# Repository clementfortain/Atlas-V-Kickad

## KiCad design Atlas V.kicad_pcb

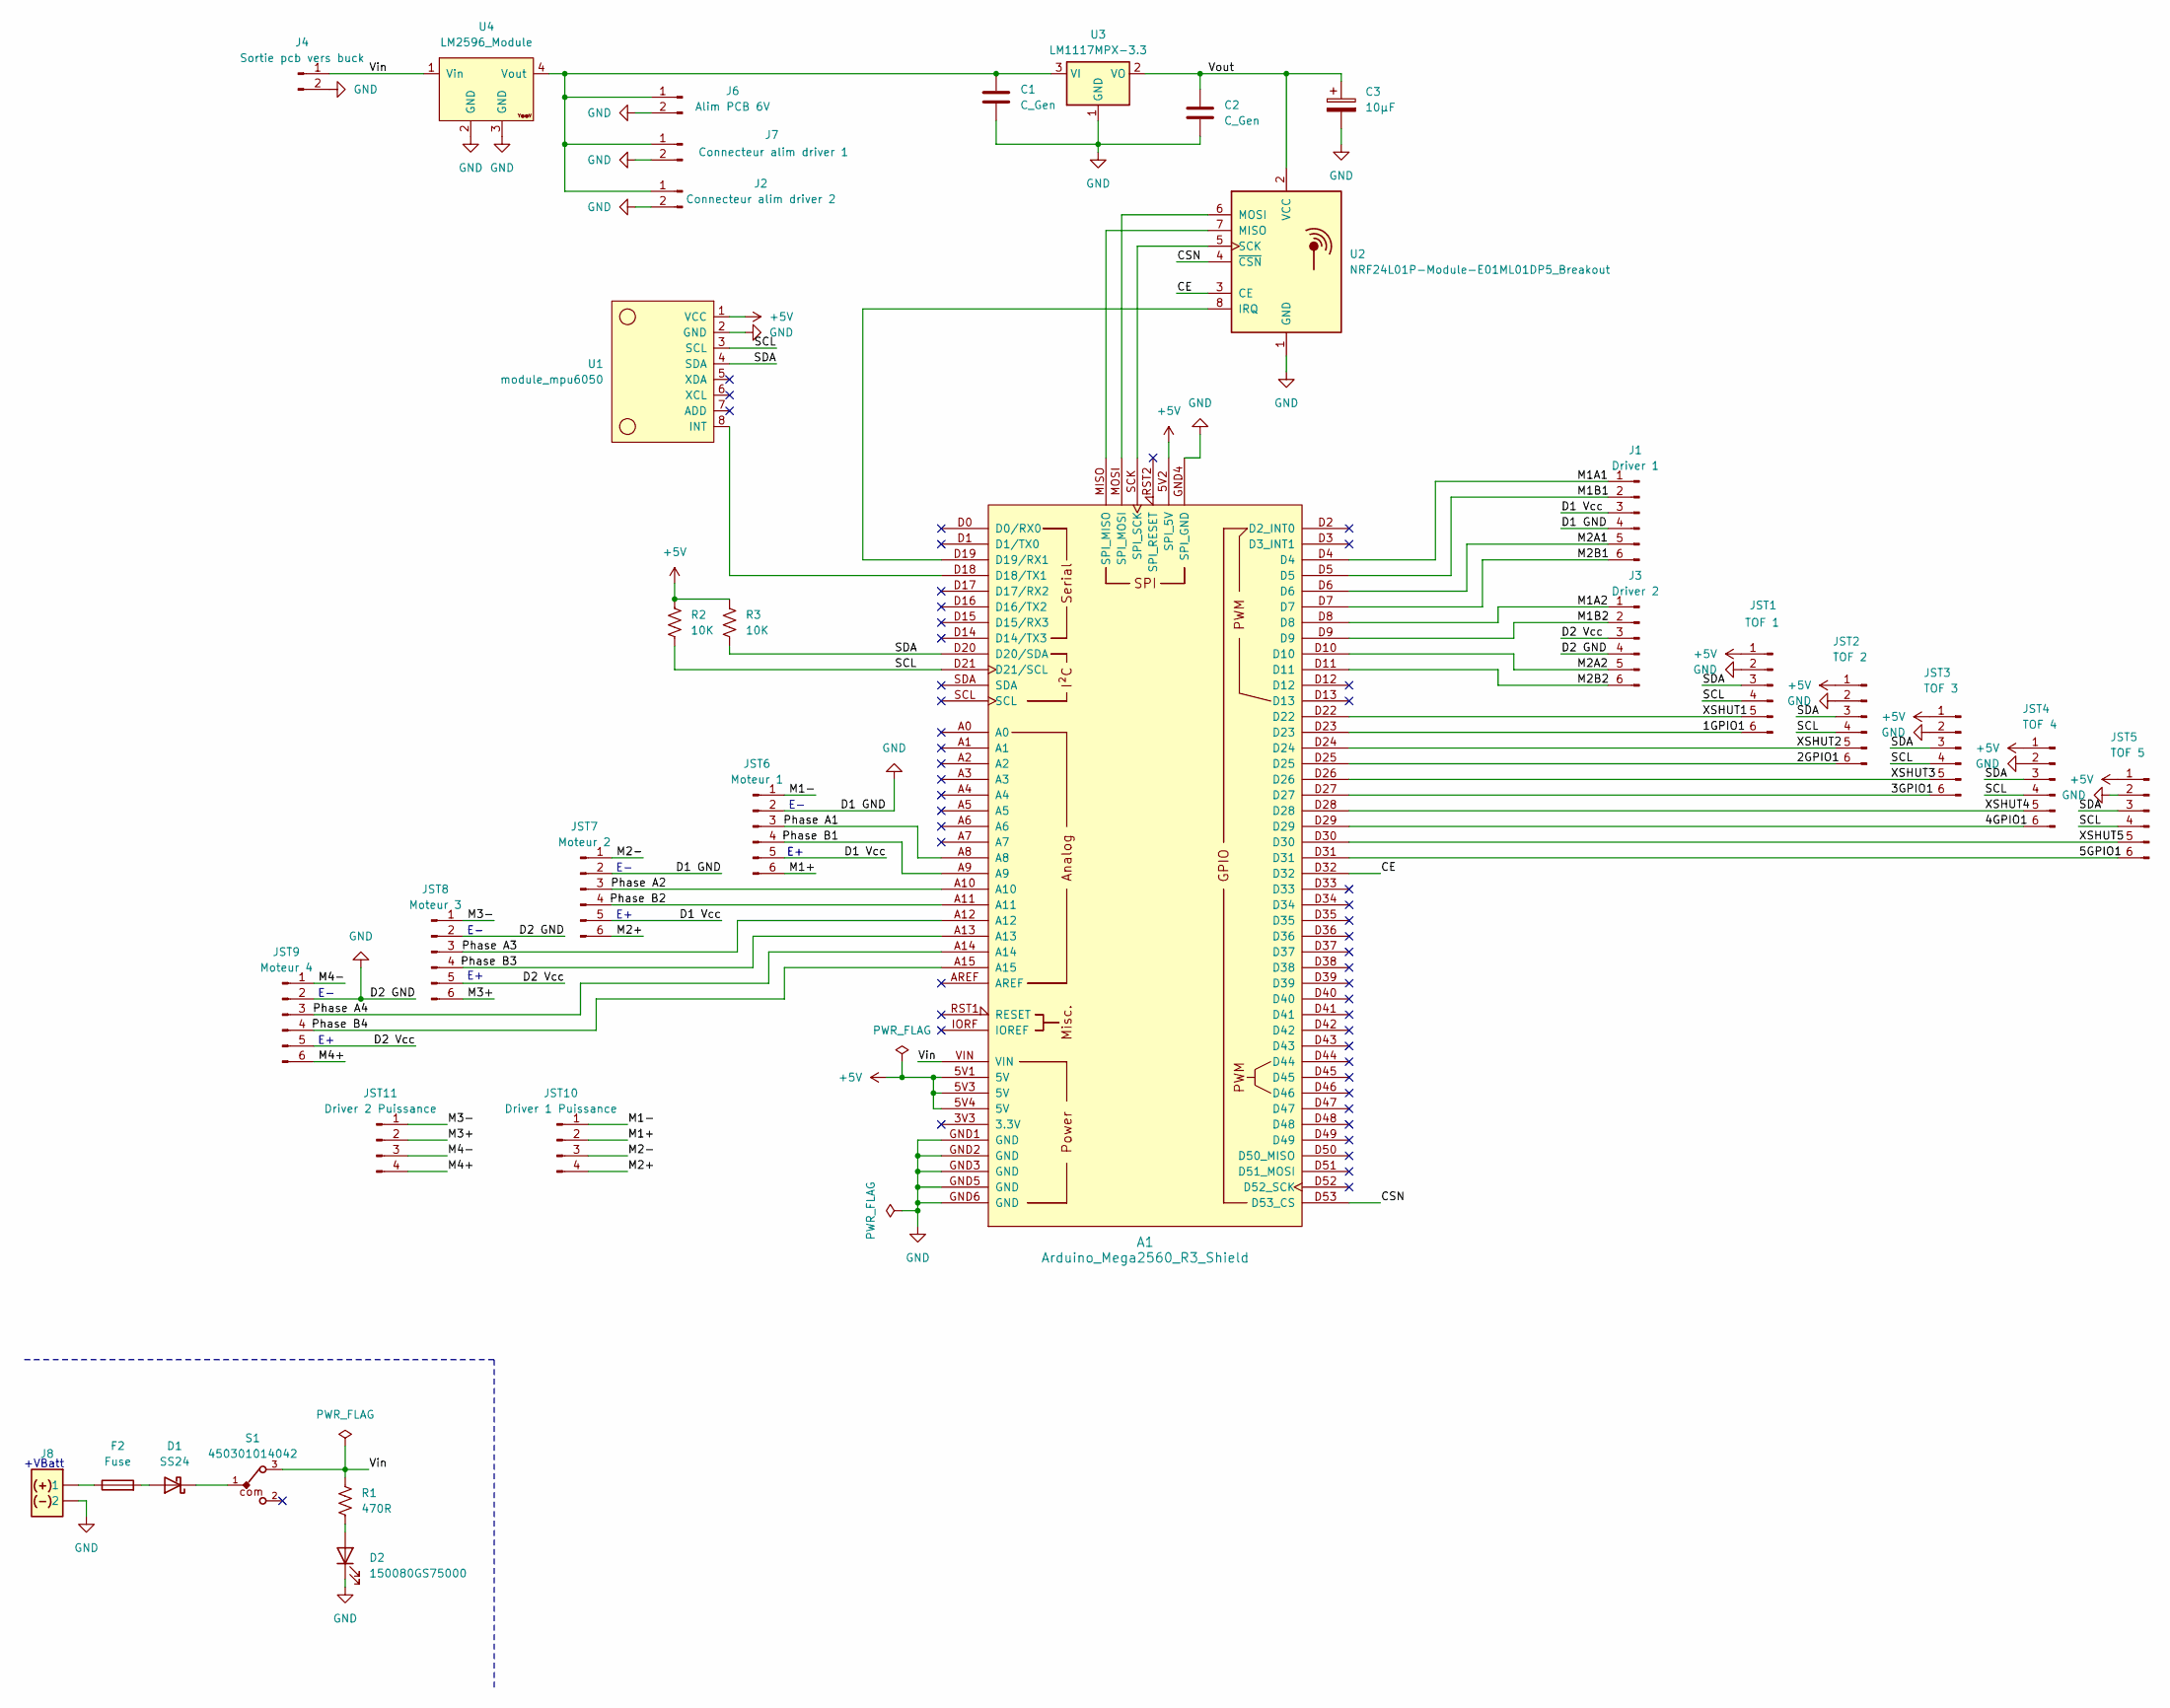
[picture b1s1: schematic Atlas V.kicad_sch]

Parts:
A1: Arduino_Mega2560_R3_Shield; Arduino_Mega2560_R3_Shield_LongPad
C1, C2: C_Gen; C_1206_3216Metric_Pad1.33x1.80mm_HandSolder
C3: 10µF; CP_EIA-6032-28_Kemet-C_Pad2.25x2.35mm_HandSolder
D1: SS24; D_SMB_Handsoldering
D2: 150080GS75000; LED_0805_2012Metric_Pad1.15x1.40mm_HandSolder
F2: Fuse; Fuseholder_TR5_Littelfuse_No560_No460
J1: Driver 1; JST_XH_B6B-XH-AM_1x06_P2.50mm_Long_Vertical
J2: Connecteur alim driver 2; JST_XH_B2B-XH-AM_1x02_P2.50mm_Long_Vertical
J3: Driver 2; JST_XH_B6B-XH-AM_1x06_P2.50mm_Long_Vertical
J4: Sortie pcb vers buck; JST_XH_B2B-XH-AM_1x02_P2.50mm_Long_Vertical
J6: Alim PCB 6V; JST_XH_B2B-XH-AM_1x02_P2.50mm_Long_Vertical
J7: Connecteur alim driver 1; JST_XH_B2B-XH-AM_1x02_P2.50mm_Long_Vertical
J8: CON 1x2 POLARIZED; AMASS_XT60-M_1x02_P7.20mm_Vertical
JST1: TOF 1; JST_XH_B6B-XH-AM_1x06_P2.50mm_Long_Vertical
JST2: TOF 2; JST_XH_B6B-XH-AM_1x06_P2.50mm_Long_Vertical
JST3: TOF 3; JST_XH_B6B-XH-AM_1x06_P2.50mm_Long_Vertical
JST4: TOF 4; JST_XH_B6B-XH-AM_1x06_P2.50mm_Long_Vertical
JST5: TOF 5; JST_XH_B6B-XH-AM_1x06_P2.50mm_Long_Vertical
JST6: Moteur 1; JST_XH_B6B-XH-AM_1x06_P2.50mm_Long_Vertical
JST7: Moteur 2; JST_XH_B6B-XH-AM_1x06_P2.50mm_Long_Vertical
JST8: Moteur 3; JST_XH_B6B-XH-AM_1x06_P2.50mm_Long_Vertical
JST9: Moteur 4; JST_XH_B6B-XH-AM_1x06_P2.50mm_Long_Vertical
JST10: Driver 1 Puissance; JST_XH_B4B-XH-AM_1x04_P2.50mm_Long_Vertical
JST11: Driver 2 Puissance; JST_XH_B4B-XH-AM_1x04_P2.50mm_Long_Vertical
R1: 470R; R_1206_3216Metric_Pad1.30x1.75mm_HandSolder
R2: 10K; R_1206_3216Metric_Pad1.30x1.75mm_HandSolder
R3: 10K; R_1206_3216Metric_Pad1.30x1.75mm_HandSolder; PartNumber Voir farde de resistance
S1: 450301014042
U1: module_mpu6050
U2: NRF24L01P-Module-E01ML01DP5_Breakout; E01-ML01DP5
U3: LM1117MPX-3.3; SOT-223-3_TabPin2
U4: LM2596_Module; StepDown_LM2596_Module_Amazon

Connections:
+5V: A1.5V1 (5V), A1.5V2 (SPI_5V), A1.5V3 (5V), A1.5V4 (5V), JST1.1, JST2.1, JST3.1, JST4.1, JST5.1, R2.1, R3.1, U1.1 (VCC)
/1GPIO1: A1.D23, JST1.6
/2GPIO1: A1.D25, JST2.6
/3GPIO1: A1.D27, JST3.6
/4GPIO1: A1.D29, JST4.6
/5GPIO1: A1.D31, JST5.6
/CE: A1.D32, U2.3 (CE)
/CSN: A1.D53 (D53_CS), U2.4 (~CSN)
/D1 Vcc: J1.3, JST6.5, JST7.5
/D2 Vcc: J3.3, JST8.5, JST9.5
/M1+: JST6.6, JST10.2
/M1-: JST6.1, JST10.1
/M1A1: A1.D4, J1.1
/M1A2: A1.D8, J3.1
/M1B1: A1.D5, J1.2
/M1B2: A1.D9, J3.2
/M2+: JST7.6, JST10.4
/M2-: JST7.1, JST10.3
/M2A1: A1.D6, J1.5
/M2A2: A1.D10, J3.5
/M2B1: A1.D7, J1.6
/M2B2: A1.D11, J3.6
/M3+: JST8.6, JST11.2
/M3-: JST8.1, JST11.1
/M4+: JST9.6, JST11.4
/M4-: JST9.1, JST11.3
/Phase A1: A1.A8, JST6.3
/Phase A2: A1.A10, JST7.3
/Phase A3: A1.A12, JST8.3
/Phase A4: A1.A14, JST9.3
/Phase B1: A1.A9, JST6.4
/Phase B2: A1.A11, JST7.4
/Phase B3: A1.A13, JST8.4
/Phase B4: A1.A15, JST9.4
/SCL: A1.D21 (D21/SCL), JST1.4, JST2.4, JST3.4, JST4.4, JST5.4, R2.2, U1.3 (SCL)
/SDA: A1.D20 (D20/SDA), JST1.3, JST2.3, JST3.3, JST4.3, JST5.3, R3.2, U1.4 (SDA)
/Vin: A1.VIN, J4.1, R1.1, S1.3, U4.1 (Vin)
/Vout: C2.1, C3.1, U2.2 (VCC), U3.2 (VO)
/XSHUT1: A1.D22, JST1.5
/XSHUT2: A1.D24, JST2.5
/XSHUT3: A1.D26, JST3.5
/XSHUT4: A1.D28, JST4.5
/XSHUT5: A1.D30, JST5.5
GND: A1.GND1 (GND), A1.GND2 (GND), A1.GND3 (GND), A1.GND4 (SPI_GND), A1.GND5 (GND), A1.GND6 (GND), C1.2, C2.2, C3.2, D2.1 (K), J1.4, J2.2, J3.4, J4.2, J6.2, J7.2, J8.2, JST1.2, JST2.2, JST3.2, JST4.2, JST5.2, JST6.2, JST7.2, JST8.2, JST9.2, U1.2 (GND), U2.1 (GND), U3.1 (GND), U4.2 (GND), U4.3 (GND)
unnamed: A1.D18 (D18/TX1), U1.8 (INT)
unnamed: A1.D19 (D19/RX1), U2.8 (IRQ)
unnamed: A1.MISO (SPI_MISO), U2.7 (MISO)
unnamed: A1.MOSI (SPI_MOSI), U2.6 (MOSI)
unnamed: A1.SCK (SPI_SCK), U2.5 (SCK)
unnamed: D1.2 (A), F2.2
unnamed: D1.1 (K), S1.1
unnamed: D2.2 (A), R1.2
unnamed: F2.1, J8.1
unnamed: C1.1, J2.1, J6.1, J7.1, U3.3 (VI), U4.4 (Vout)

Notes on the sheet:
+VBatt

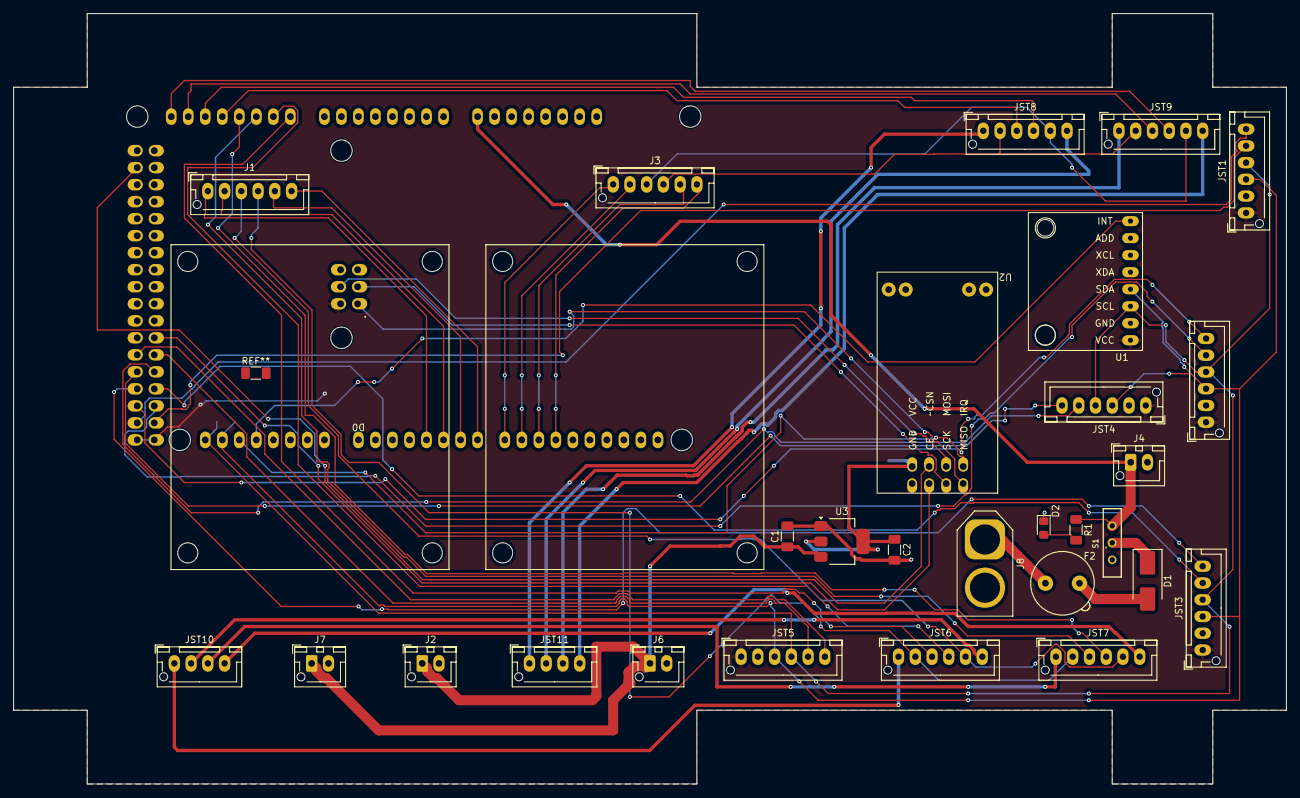
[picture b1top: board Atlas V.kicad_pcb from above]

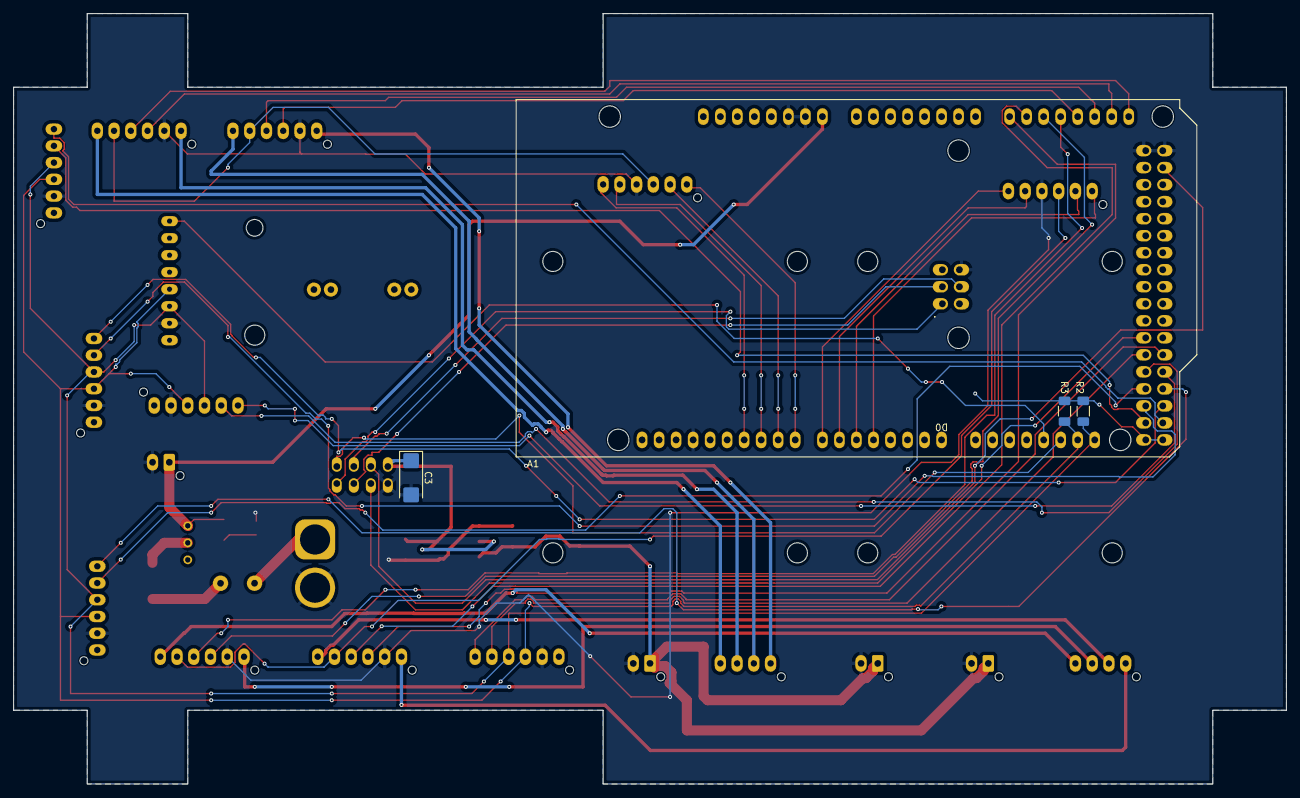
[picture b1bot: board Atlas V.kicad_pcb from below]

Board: 2 copper layers, 190.0 x 115.0 mm, 32 parts (3 on the bottom side), 54 nets.

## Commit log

2026-04-21 Ajout readme
2026-04-21 Kickad
2026-04-24 PCB presque fini
2026-04-24 PCB terminé
2026-04-26 PCB Terminé V2
2026-04-29 Quelques modifications à discuter de vive voix
